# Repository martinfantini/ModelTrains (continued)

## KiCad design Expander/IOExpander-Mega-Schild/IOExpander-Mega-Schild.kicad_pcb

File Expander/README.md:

# Expander

This repository contains all the necesarry information for generate an expander of the possible input/output of the central.

## IO-Expander

For this case, I use also the [EX-IOExpander](https://github.com/DCC-EX/EX-IOExpander)

## Generic-Mega-Schild

For my case, I yunse Arduino Mega shild to generate the expander. To have more clean, the expande, I generate a circuit borad to solder all the input cables.

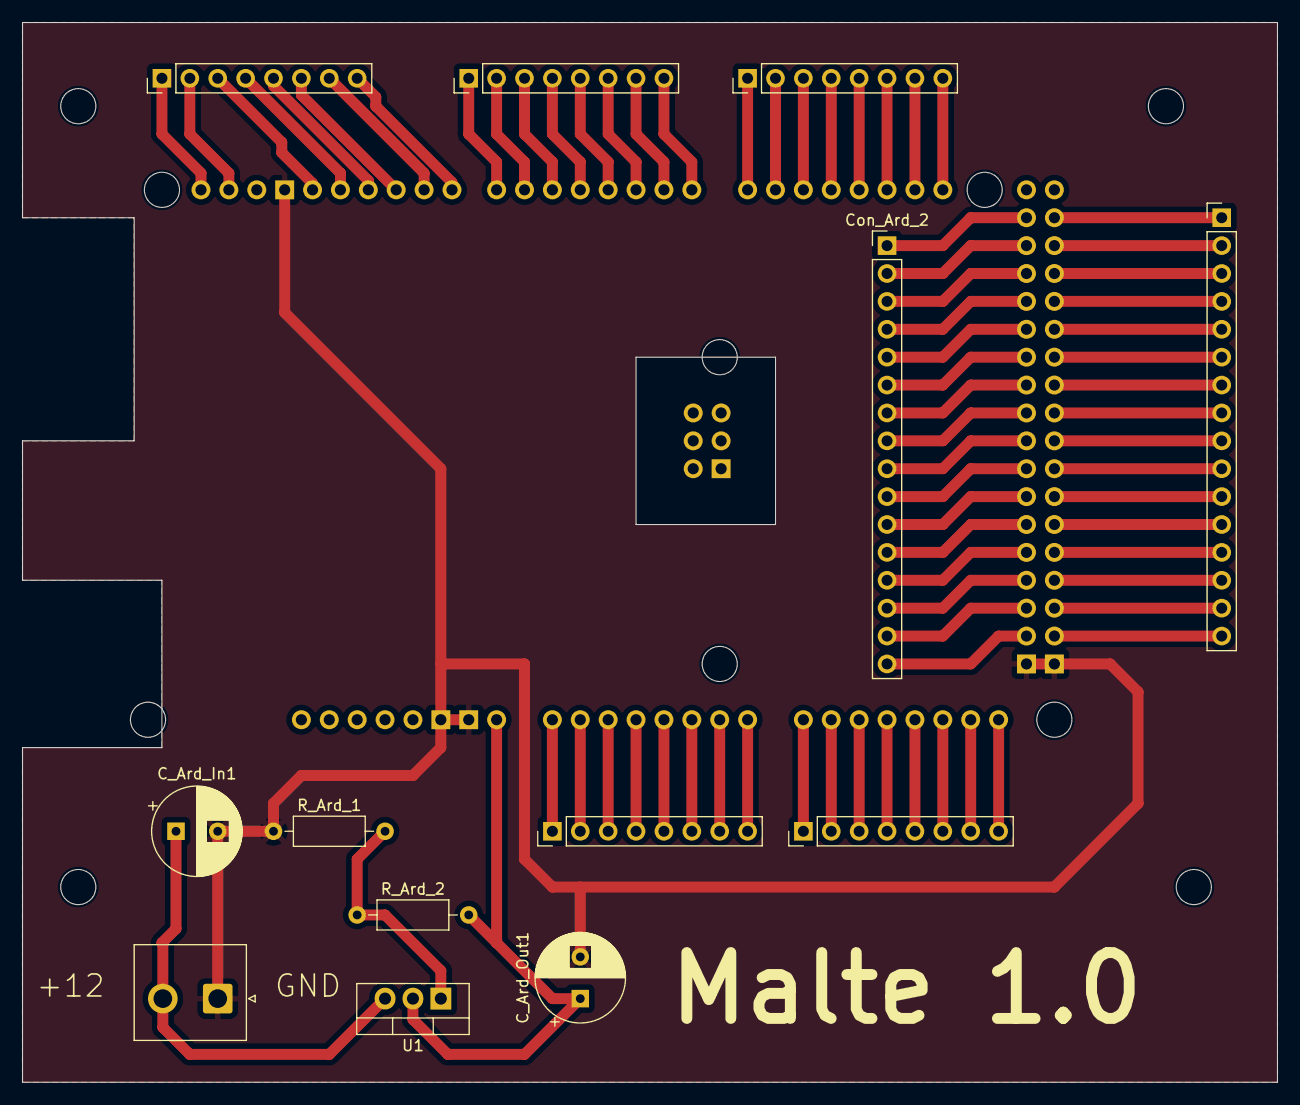
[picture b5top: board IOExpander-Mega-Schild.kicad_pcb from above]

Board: 2 copper layers, 114.3 x 96.5 mm, 14 parts (0 on the bottom side), 76 nets.

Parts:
CON_In1: DCC; JST_NV_B02P-NV_1x02_P5.00mm_Vertical
C_Ard_In1: 10uF; CP_Radial_D8.0mm_P3.80mm
C_Ard_Out1: 10uF; CP_Radial_D8.0mm_P3.80mm
Central1: Arduino_Mega2560_Shield
Con_Ard_2, Con_Ard_3: Conn_01x16; PinHeader_1x16_P2.54mm_Vertical
J1, J2, J3, J4, J5: Conn_01x08; PinHeader_1x08_P2.54mm_Vertical
R_Ard_1: 3K9; R_Axial_DIN0207_L6.3mm_D2.5mm_P10.16mm_Horizontal
R_Ard_2: 560; R_Axial_DIN0207_L6.3mm_D2.5mm_P10.16mm_Horizontal
U1: LD1086V-DG; TO-220-3_Vertical

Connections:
+12V: CON_In1.2, C_Ard_In1.1, U1.3 (IN)
Earth: CON_In1.1, C_Ard_In1.2, C_Ard_Out1.2, Central1.GND1 (GND), Central1.GND2 (GND), Central1.GND3 (GND), Central1.GND5 (GND), Central1.GND6 (GND), R_Ard_1.1
unnamed: Central1.D0 (D0_RX0), J4.8
unnamed: Central1.D1 (D1_TX0), J4.7
unnamed: Central1.D2 (D2_INT0), J4.6
unnamed: Central1.D3 (D3_INT1), J4.5
unnamed: Central1.D14 (D14_TX3), J3.1
unnamed: Central1.D15 (D15_RX3), J3.2
unnamed: Central1.D16 (D16_TX2), J3.3
unnamed: Central1.D17 (D17_RX2), J3.4
unnamed: Central1.D18 (D18_TX1), J3.5
unnamed: Central1.D19 (D19_RX1), J3.6
unnamed: Central1.D20 (D20_SDA), J3.7
unnamed: Central1.D21 (D21_SCL), J3.8
unnamed: Central1.D53 (D53_SS), Con_Ard_3.16
unnamed: Central1.D22, Con_Ard_2.1
unnamed: Central1.D24, Con_Ard_2.2
unnamed: Central1.D26, Con_Ard_2.3
unnamed: Central1.D28, Con_Ard_2.4
unnamed: Central1.D30, Con_Ard_2.5
unnamed: Central1.D32, Con_Ard_2.6
unnamed: Central1.D34, Con_Ard_2.7
unnamed: Central1.D36, Con_Ard_2.8
unnamed: Central1.D38, Con_Ard_2.9
unnamed: Central1.D40, Con_Ard_2.10
unnamed: Central1.D42, Con_Ard_2.11
unnamed: Central1.D44, Con_Ard_2.12
unnamed: Central1.D46, Con_Ard_2.13
unnamed: Central1.D48, Con_Ard_2.14
unnamed: Central1.D50, Con_Ard_2.15
unnamed: Central1.D52, Con_Ard_2.16
unnamed: Central1.D23, Con_Ard_3.1
unnamed: Central1.D25, Con_Ard_3.2
unnamed: Central1.D27, Con_Ard_3.3
unnamed: Central1.D29, Con_Ard_3.4
unnamed: Central1.D31, Con_Ard_3.5
unnamed: Central1.D33, Con_Ard_3.6
unnamed: Central1.D35, Con_Ard_3.7
unnamed: Central1.D37, Con_Ard_3.8
unnamed: Central1.D39, Con_Ard_3.9
unnamed: Central1.D41, Con_Ard_3.10
unnamed: Central1.D43, Con_Ard_3.11
unnamed: Central1.D45, Con_Ard_3.12
unnamed: Central1.D47, Con_Ard_3.13
unnamed: Central1.D49, Con_Ard_3.14
unnamed: Central1.D51, Con_Ard_3.15
unnamed: Central1.A0, J1.1
unnamed: Central1.A1, J1.2
unnamed: Central1.A2, J1.3
unnamed: Central1.A3, J1.4
unnamed: Central1.A4, J1.5
unnamed: Central1.A5, J1.6
unnamed: Central1.A6, J1.7
unnamed: Central1.A7, J1.8
unnamed: Central1.A8, J2.1
unnamed: Central1.A9, J2.2
unnamed: Central1.A10, J2.3
unnamed: Central1.A11, J2.4
unnamed: Central1.A12, J2.5
unnamed: Central1.A13, J2.6
unnamed: Central1.A14, J2.7
unnamed: Central1.A15, J2.8
unnamed: Central1.D7, J4.1
unnamed: Central1.D6, J4.2
unnamed: Central1.D5, J4.3
unnamed: Central1.D4, J4.4
unnamed: Central1.SCL, J5.1
unnamed: Central1.SDA, J5.2
unnamed: Central1.D13, J5.3
unnamed: Central1.D12, J5.4
unnamed: Central1.D11, J5.5
unnamed: Central1.D10, J5.6
unnamed: Central1.D9, J5.7
unnamed: Central1.D8, J5.8
unnamed: R_Ard_1.2, R_Ard_2.1, U1.1 (ADJ/GND)
unnamed: C_Ard_Out1.1, Central1.VIN, R_Ard_2.2, U1.2 (OUT)

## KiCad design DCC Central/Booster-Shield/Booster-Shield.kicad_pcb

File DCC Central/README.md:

# DCC Central

As a DCC central, I use the open source project [CommandStation-EX](https://github.com/DCC-EX/CommandStation-EX), here is added as asubmodule up this project.
Usigin Arduino ATMega 328, I generate a booster with the use of the motor diver [BTS7960](./'BTS7960 Motor Driver.pdf')

## CommandStation-EX

Here is the CommandStation-EX project used to generate the DCC central, which will be user to control all the trains and diferent periferics asociated to the DCC protocol.

## Booster

In this folder contains the source code to coltrol the booster with the ATMega 328.

## Booster-Shield

In this folder contains the circuit board to control the [motor driver](./'BTS7960 Motor Driver.pdf')

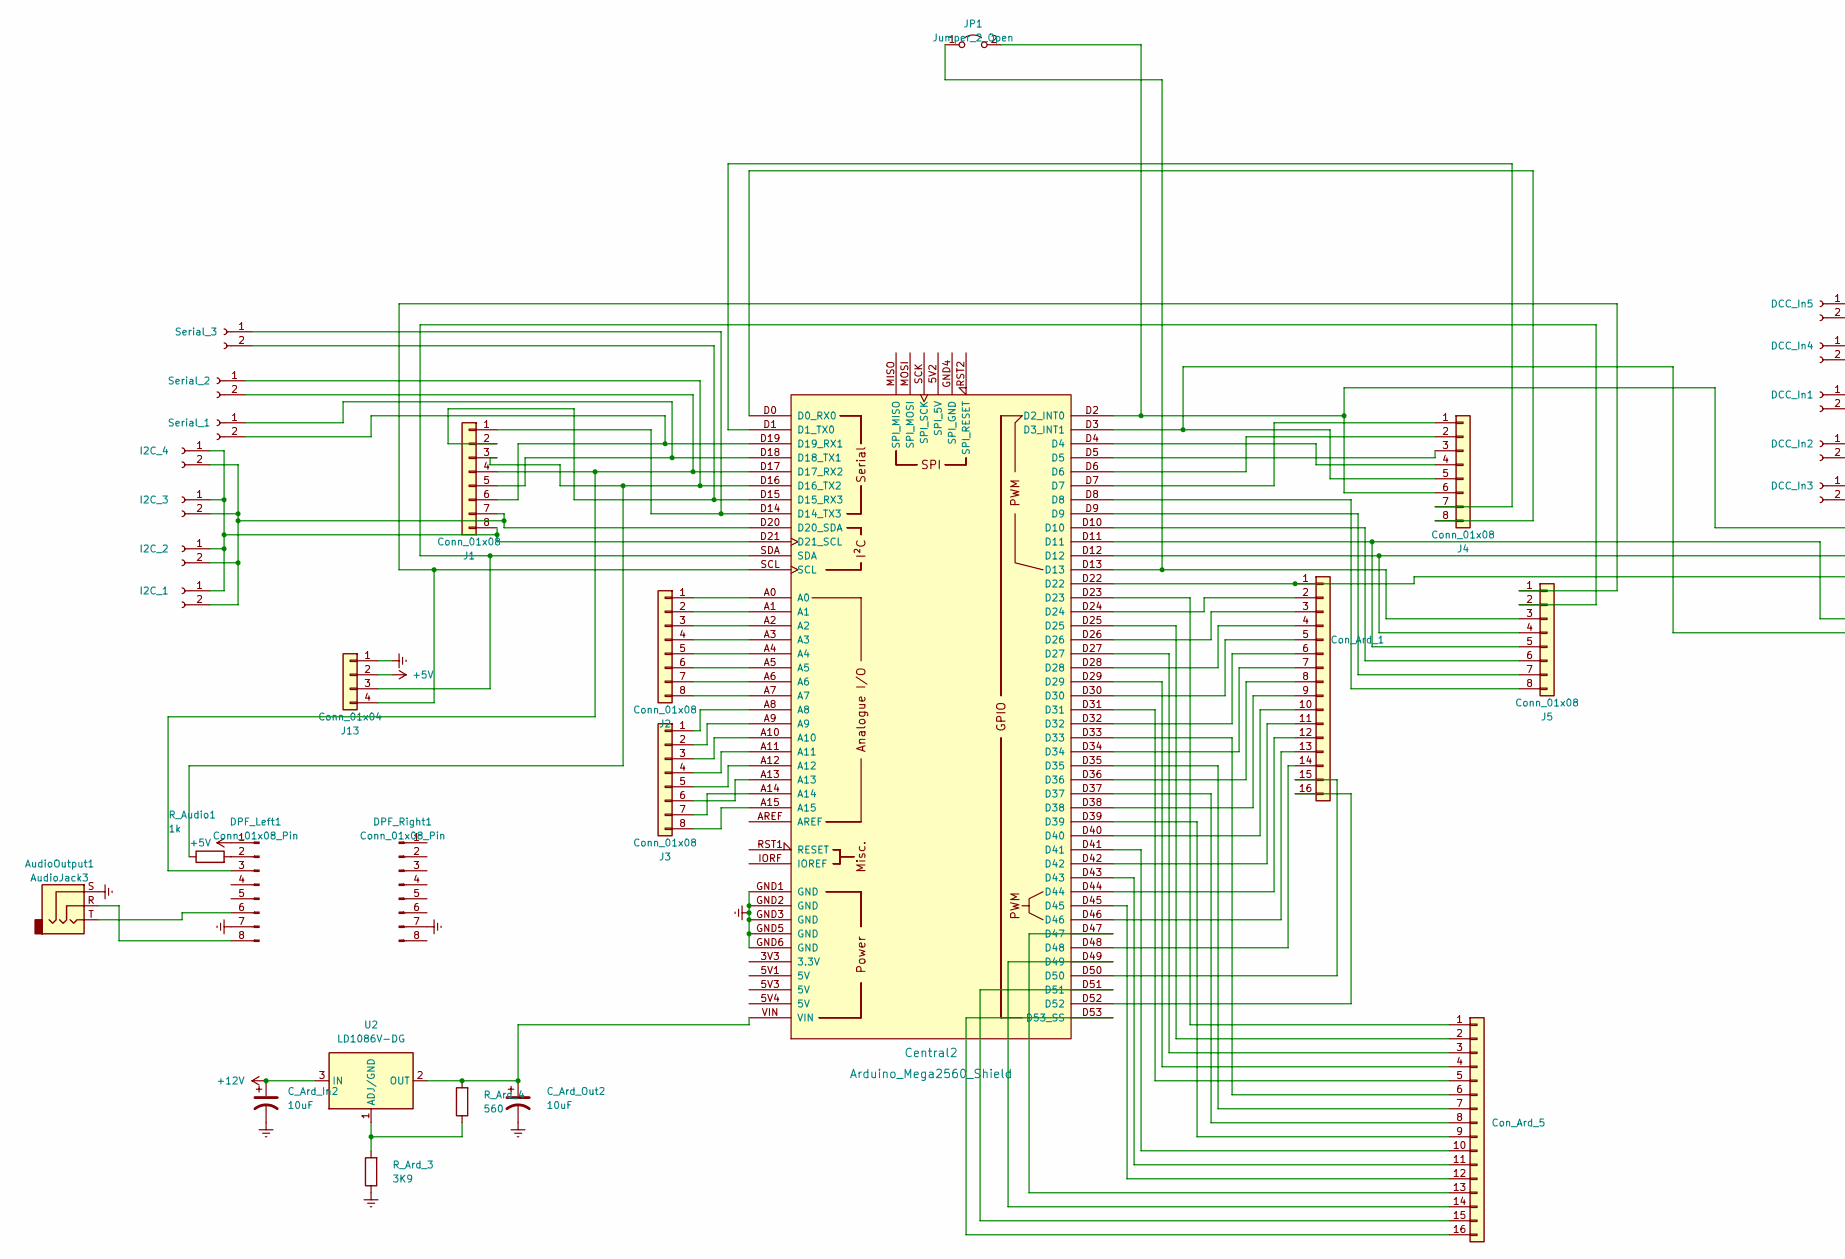
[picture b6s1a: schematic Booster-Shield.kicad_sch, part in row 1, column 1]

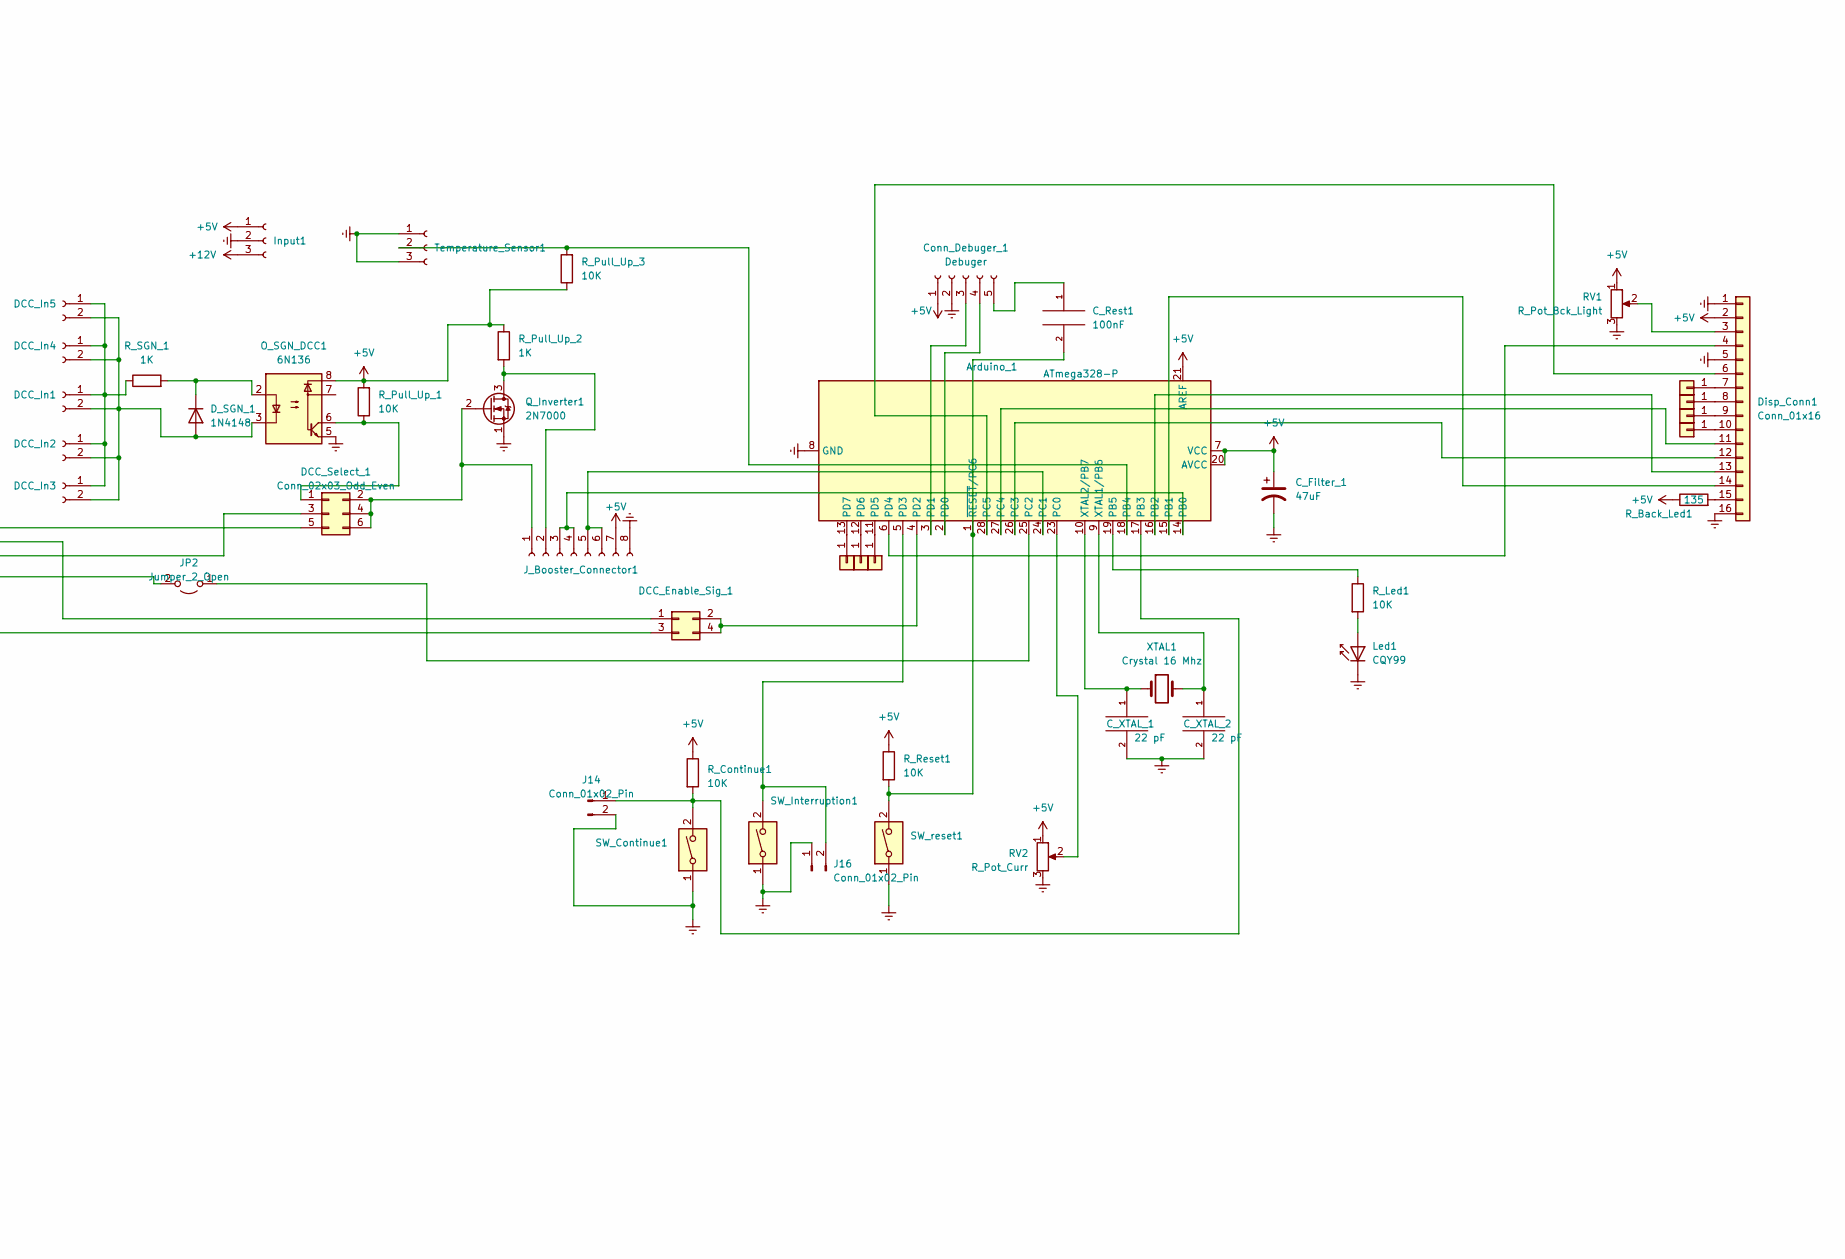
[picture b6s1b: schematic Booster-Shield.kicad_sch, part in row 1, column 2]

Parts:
Arduino_1: ATmega328-P; DIP-28_W7.62mm
AudioOutput1: AudioJack3; Jack_3.5mm_CUI_SJ1-3523N_Horizontal
C_Ard_In2: 10uF; CP_Radial_D8.0mm_P3.80mm
C_Ard_Out2: 10uF; CP_Radial_D8.0mm_P3.80mm
C_Filter_1: 47uF; CP_Radial_D8.0mm_P3.80mm
C_Rest1: 100nF; C_2225_5664Metric_Pad1.80x6.60mm_HandSolder
C_XTAL_1, C_XTAL_2: 22 pF; C_Disc_D8.0mm_W5.0mm_P5.00mm
Central2: Arduino_Mega2560_Shield
Con_Ard_1, Con_Ard_5: Conn_01x16; PinHeader_1x16_P2.54mm_Vertical
Conn_Debuger_1: Debuger; PinHeader_1x05_P2.54mm_Vertical
DCC_Enable_Sig_1: Conn_02x02_Odd_Even; PinHeader_2x02_P2.54mm_Vertical
DCC_In1, DCC_In2, DCC_In3, DCC_In4, DCC_In5: DCC; Wago_734-132_1x02_P3.50mm_Vertical
DCC_Select_1: Conn_02x03_Odd_Even; PinHeader_2x03_P2.54mm_Vertical
DPF_Left1: Conn_01x08_Pin; PinHeader_1x08_P2.54mm_Vertical
DPF_Right1: Conn_01x08_Pin; PinHeader_1x08_P2.54mm_Vertical
D_SGN_1: 1N4148; D_DO-35_SOD27_P7.62mm_Horizontal
Disp_Conn1: Conn_01x16; PinHeader_1x16_P2.54mm_Vertical
I2C_1, I2C_2, I2C_3, I2C_4: I2C; Wago_734-132_1x02_P3.50mm_Vertical
Input1: Conn_01x03_Female; JST_NV_B03P-NV_1x03_P5.00mm_Vertical
J1, J2, J3, J4, J5: Conn_01x08; PinHeader_1x08_P2.54mm_Vertical
J6, J7, J8, J9, J10, J11, J12: Conn_01x01; PinHeader_1x01_P2.54mm_Vertical
J13: Conn_01x04; PinHeader_1x04_P2.54mm_Vertical
J14, J16: Conn_01x02_Pin; PinHeader_1x02_P2.54mm_Vertical
JP1, JP2: Jumper_2_Open; SolderJumper-2_P1.3mm_Open_Pad1.0x1.5mm
J_Booster_Connector1: Conn_01x08_Female; PinHeader_2x04_P2.54mm_Vertical
Led1: CQY99; LED_D5.0mm_IRGrey
O_SGN_DCC1: 6N136; DIP-8_W7.62mm
Q_Inverter1: 2N7000; TO-92_Inline
RV1: R_Pot_Bck_Light; Potentiometer_ACP_CA6-H2,5_Horizontal
RV2: R_Pot_Curr; Potentiometer_ACP_CA6-H2,5_Horizontal
R_Ard_3: 3K9; R_Axial_DIN0207_L6.3mm_D2.5mm_P10.16mm_Horizontal
R_Ard_4: 560; R_Axial_DIN0207_L6.3mm_D2.5mm_P10.16mm_Horizontal
R_Audio1: 1k; R_Axial_DIN0207_L6.3mm_D2.5mm_P10.16mm_Horizontal
R_Back_Led1: 135; R_Axial_DIN0207_L6.3mm_D2.5mm_P10.16mm_Horizontal
R_Continue1: 10K; R_Axial_DIN0207_L6.3mm_D2.5mm_P10.16mm_Horizontal
R_Led1: 10K; R_Axial_DIN0207_L6.3mm_D2.5mm_P10.16mm_Horizontal
R_Pull_Up_1, R_Pull_Up_3: 10K; R_Axial_DIN0207_L6.3mm_D2.5mm_P10.16mm_Horizontal
R_Pull_Up_2: 1K; R_Axial_DIN0207_L6.3mm_D2.5mm_P10.16mm_Horizontal
R_Reset1: 10K; R_Axial_DIN0207_L6.3mm_D2.5mm_P10.16mm_Horizontal
R_SGN_1: 1K; R_Axial_DIN0207_L6.3mm_D2.5mm_P10.16mm_Horizontal
SW_Continue1: SW_DIP_x01; SW_PUSH_6mm_H5mm
SW_Interruption1: SW_DIP_x01; SW_PUSH_6mm_H5mm
SW_reset1: SW_DIP_x01; SW_PUSH_6mm_H5mm
Serial_1, Serial_2, Serial_3: Serial; Wago_734-132_1x02_P3.50mm_Vertical
Temperature_Sensor1: Conn_01x03_Female; JST_EH_B3B-EH-A_1x03_P2.50mm_Vertical
U2: LD1086V-DG; TO-220-3_Vertical
XTAL1: Crystal 16 Mhz; Crystal_HC49-U_Vertical

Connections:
+5V: Arduino_1.7 (VCC), Arduino_1.20 (AVCC), Arduino_1.21 (AREF), C_Filter_1.1, Conn_Debuger_1.1, DPF_Left1.1, Disp_Conn1.2, Input1.1, J13.2, J_Booster_Connector1.7, O_SGN_DCC1.8, RV1.1, RV2.1, R_Back_Led1.1, R_Continue1.1, R_Pull_Up_1.2, R_Pull_Up_2.1, R_Pull_Up_3.1, R_Reset1.1
+12V: C_Ard_In2.1, Input1.3, U2.3 (IN)
Earth: Arduino_1.8 (GND), Arduino_1.22 (GND), AudioOutput1.S, C_Ard_In2.2, C_Ard_Out2.2, C_Filter_1.2, C_XTAL_1.2, C_XTAL_2.2, Central2.GND1 (GND), Central2.GND2 (GND), Central2.GND3 (GND), Central2.GND5 (GND), Central2.GND6 (GND), Conn_Debuger_1.2, DPF_Left1.7, DPF_Right1.7, Disp_Conn1.1, Disp_Conn1.5, Disp_Conn1.16, Input1.2, J13.1, J14.2, J16.1, J_Booster_Connector1.8, Led1.1 (K), O_SGN_DCC1.5, Q_Inverter1.1 (S), RV1.3, RV2.3, R_Ard_3.1, SW_Continue1.1, SW_Interruption1.1, SW_reset1.1, Temperature_Sensor1.1, Temperature_Sensor1.3
unnamed: Arduino_1.14 (PB0), J_Booster_Connector1.3, J_Booster_Connector1.4
unnamed: Arduino_1.15 (PB1), Disp_Conn1.14
unnamed: Arduino_1.16 (PB2), Disp_Conn1.13
unnamed: Arduino_1.17 (PB3), J14.1, R_Continue1.2, SW_Continue1.2
unnamed: Arduino_1.18 (PB4), R_Pull_Up_3.2, Temperature_Sensor1.2
unnamed: Arduino_1.19 (PB5), R_Led1.1
unnamed: Arduino_1.23 (PC0), RV2.2
unnamed: Arduino_1.24 (PC1), J_Booster_Connector1.5, J_Booster_Connector1.6
unnamed: Arduino_1.25 (PC2), JP2.1 (A)
unnamed: Arduino_1.26 (PC3), Disp_Conn1.12
unnamed: Arduino_1.27 (PC4), Disp_Conn1.11
unnamed: Arduino_1.28 (PC5), Disp_Conn1.6
unnamed: Arduino_1.2 (PD0), Conn_Debuger_1.4
unnamed: Arduino_1.3 (PD1), Conn_Debuger_1.3
unnamed: Arduino_1.4 (PD2), DCC_Enable_Sig_1.2, DCC_Enable_Sig_1.4
unnamed: Arduino_1.5 (PD3), J16.2, SW_Interruption1.2
unnamed: Arduino_1.6 (PD4), Disp_Conn1.4
unnamed: Arduino_1.11 (PD5), J6.1
unnamed: Arduino_1.12 (PD6), J7.1
unnamed: Arduino_1.13 (PD7), J8.1
unnamed: Arduino_1.9 (XTAL1/PB6), C_XTAL_2.1, XTAL1.2
unnamed: Arduino_1.10 (XTAL2/PB7), C_XTAL_1.1, XTAL1.1
unnamed: Arduino_1.1 (~RESET/PC6), C_Rest1.2, R_Reset1.2, SW_reset1.2
unnamed: Central2.D0 (D0_RX0), J4.8
unnamed: Central2.D1 (D1_TX0), J4.7
unnamed: Central2.D2 (D2_INT0), DCC_Select_1.5, J4.6, JP1.2 (B)
unnamed: Central2.D3 (D3_INT1), DCC_Enable_Sig_1.3, J4.5
unnamed: Central2.D14 (D14_TX3), J1.1, Serial_3.1
unnamed: Central2.D15 (D15_RX3), J1.2, Serial_3.2
unnamed: Central2.D16 (D16_TX2), J1.3, R_Audio1.1, Serial_2.1
unnamed: Central2.D17 (D17_RX2), DPF_Left1.3, J1.4, Serial_2.2
unnamed: Central2.D18 (D18_TX1), J1.5, Serial_1.1
unnamed: Central2.D19 (D19_RX1), J1.6, Serial_1.2
unnamed: Central2.D20 (D20_SDA), I2C_1.2, I2C_2.2, I2C_3.2, I2C_4.2, J1.7
unnamed: Central2.D21 (D21_SCL), I2C_1.1, I2C_2.1, I2C_3.1, I2C_4.1, J1.8
unnamed: Central2.D53 (D53_SS), Con_Ard_5.16
unnamed: Central2.D22, Con_Ard_1.1, JP2.2 (B)
unnamed: Central2.D24, Con_Ard_1.2
unnamed: Central2.D26, Con_Ard_1.3
unnamed: Central2.D28, Con_Ard_1.4
unnamed: Central2.D30, Con_Ard_1.5
unnamed: Central2.D32, Con_Ard_1.6
unnamed: Central2.D34, Con_Ard_1.7
unnamed: Central2.D36, Con_Ard_1.8
unnamed: Central2.D38, Con_Ard_1.9
unnamed: Central2.D40, Con_Ard_1.10
unnamed: Central2.D42, Con_Ard_1.11
unnamed: Central2.D44, Con_Ard_1.12
unnamed: Central2.D46, Con_Ard_1.13
unnamed: Central2.D48, Con_Ard_1.14
unnamed: Central2.D50, Con_Ard_1.15
unnamed: Central2.D52, Con_Ard_1.16
unnamed: Central2.D23, Con_Ard_5.1
unnamed: Central2.D25, Con_Ard_5.2
unnamed: Central2.D27, Con_Ard_5.3
unnamed: Central2.D29, Con_Ard_5.4
unnamed: Central2.D31, Con_Ard_5.5
unnamed: Central2.D33, Con_Ard_5.6
unnamed: Central2.D35, Con_Ard_5.7
unnamed: Central2.D37, Con_Ard_5.8
unnamed: Central2.D39, Con_Ard_5.9
unnamed: Central2.D41, Con_Ard_5.10
unnamed: Central2.D43, Con_Ard_5.11
unnamed: Central2.D45, Con_Ard_5.12
unnamed: Central2.D47, Con_Ard_5.13
unnamed: Central2.D49, Con_Ard_5.14
unnamed: Central2.D51, Con_Ard_5.15
unnamed: C_Rest1.1, Conn_Debuger_1.5
unnamed: Central2.D11, DCC_Enable_Sig_1.1, J5.5
unnamed: DCC_In1.1, DCC_In2.1, DCC_In3.1, DCC_In4.1, DCC_In5.1, R_SGN_1.1
unnamed: DCC_In1.2, DCC_In2.2, DCC_In3.2, DCC_In4.2, DCC_In5.2, D_SGN_1.2 (A), O_SGN_DCC1.3
unnamed: DCC_Select_1.1, O_SGN_DCC1.6, R_Pull_Up_1.1
unnamed: DCC_Select_1.2, DCC_Select_1.4, DCC_Select_1.6, J_Booster_Connector1.1, Q_Inverter1.2 (G)
unnamed: Central2.D12, DCC_Select_1.3, J5.4
unnamed: DPF_Left1.2, R_Audio1.2
unnamed: AudioOutput1.T, DPF_Left1.6
unnamed: AudioOutput1.R, DPF_Left1.8
unnamed: D_SGN_1.1 (K), O_SGN_DCC1.2, R_SGN_1.2
unnamed: Disp_Conn1.3, RV1.2
unnamed: Disp_Conn1.7, J9.1
unnamed: Disp_Conn1.8, J10.1
unnamed: Disp_Conn1.9, J11.1
unnamed: Disp_Conn1.10, J12.1
unnamed: Disp_Conn1.15, R_Back_Led1.2
unnamed: Central2.A0, J2.1
unnamed: Central2.A1, J2.2
unnamed: Central2.A2, J2.3
unnamed: Central2.A3, J2.4
unnamed: Central2.A4, J2.5
unnamed: Central2.A5, J2.6
unnamed: Central2.A6, J2.7
unnamed: Central2.A7, J2.8
unnamed: Central2.A8, J3.1
unnamed: Central2.A9, J3.2
unnamed: Central2.A10, J3.3
unnamed: Central2.A11, J3.4
unnamed: Central2.A12, J3.5
unnamed: Central2.A13, J3.6
unnamed: Central2.A14, J3.7
unnamed: Central2.A15, J3.8
unnamed: Central2.D7, J4.1
unnamed: Central2.D6, J4.2
unnamed: Central2.D5, J4.3
unnamed: Central2.D4, J4.4
unnamed: Central2.D13, J5.3, JP1.1 (A)
unnamed: Central2.D10, J5.6
unnamed: Central2.D9, J5.7
unnamed: Central2.D8, J5.8
unnamed: Central2.SDA, J5.2, J13.3
unnamed: Central2.SCL, J5.1, J13.4
unnamed: J_Booster_Connector1.2, Q_Inverter1.3 (D), R_Pull_Up_2.2
unnamed: Led1.2 (A), R_Led1.2
unnamed: R_Ard_3.2, R_Ard_4.1, U2.1 (ADJ/GND)
unnamed: C_Ard_Out2.1, Central2.VIN, R_Ard_4.2, U2.2 (OUT)

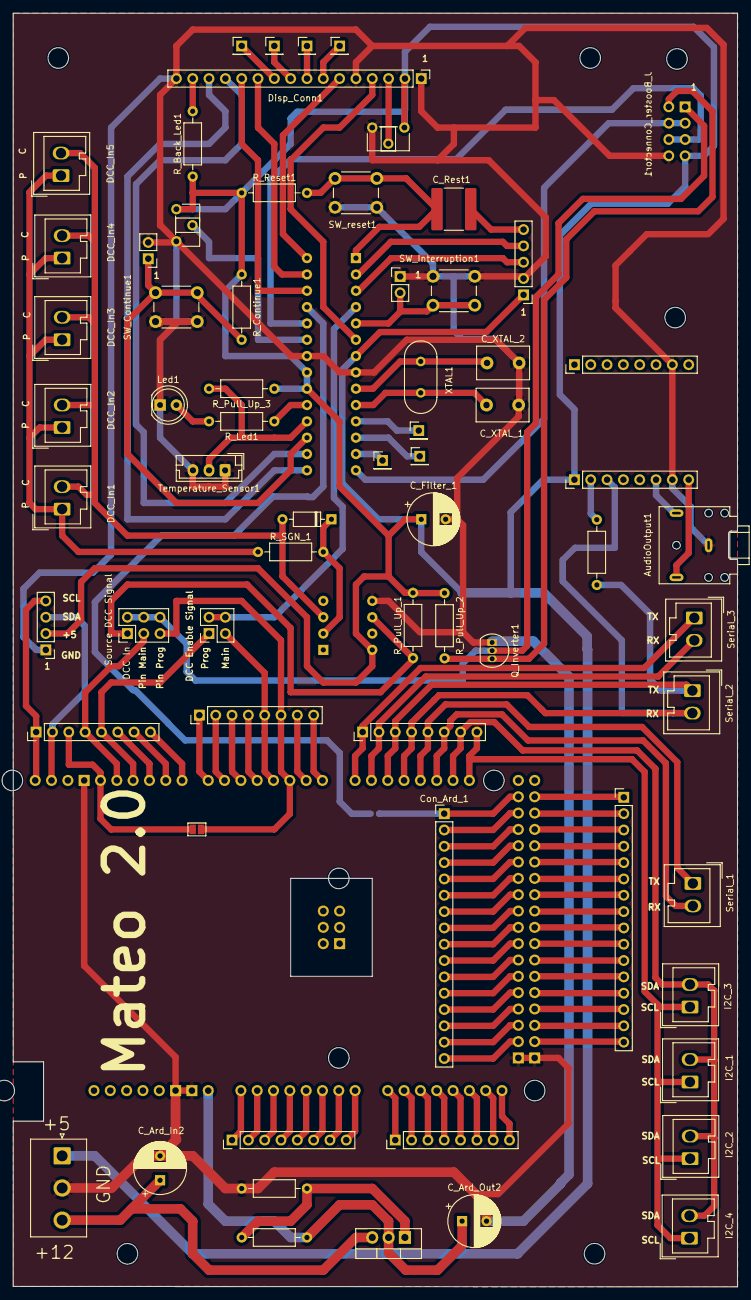
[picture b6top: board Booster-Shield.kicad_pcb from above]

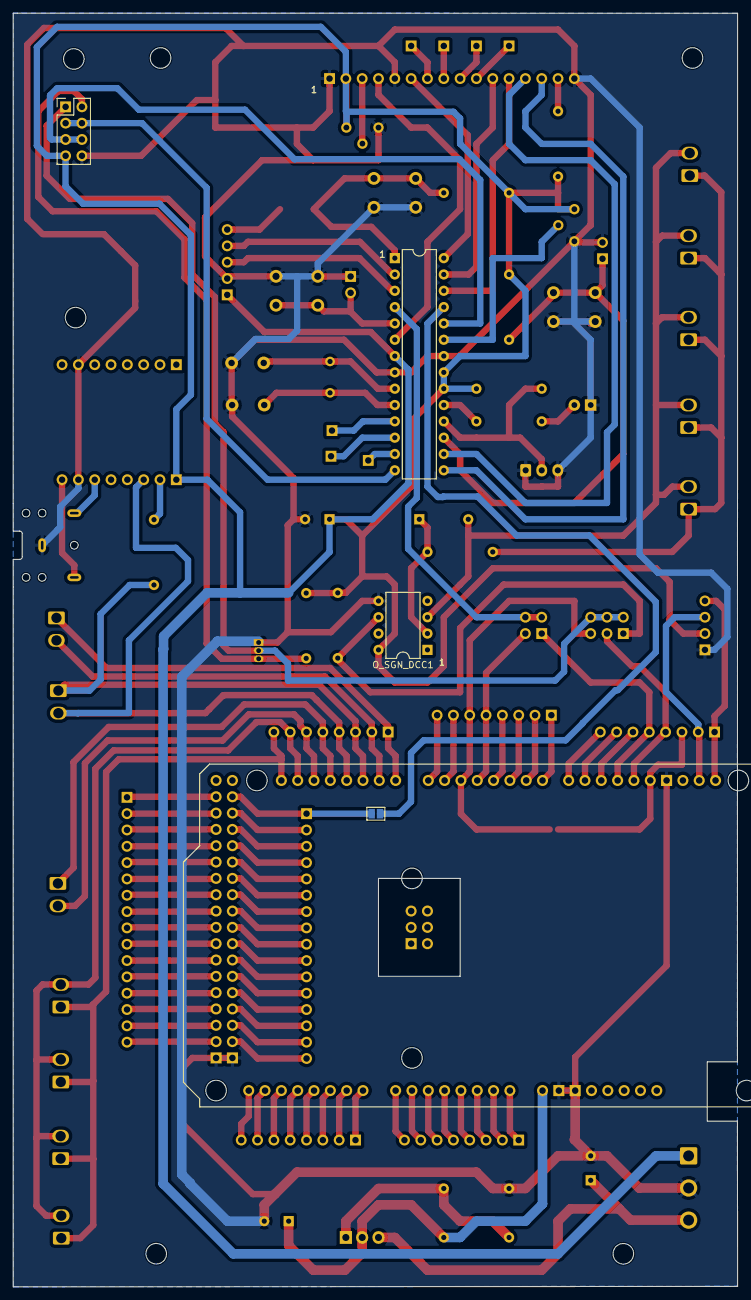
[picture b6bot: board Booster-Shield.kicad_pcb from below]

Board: 2 copper layers, 112.7 x 198.2 mm, 71 parts (4 on the bottom side), 117 nets.

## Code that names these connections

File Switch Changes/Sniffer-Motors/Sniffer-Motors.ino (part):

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#define DEBUG_DCC

//DCC Signal
#define DCC_ACK_SIGNAL 3  // Pin 5 - PD3
#define DCC_PIN_IN     2  // Pin 4 - PD2

//Motor 1
#define PIN_MOTOR_1_PIN_1 7 // Pin 13 - PD7
#define PIN_MOTOR_1_PIN_2 6 // Pin 12 - PD6

//Motor 2
#define PIN_MOTOR_2_PIN_1 4 // Pin 11 - PD5
#define PIN_MOTOR_2_PIN_2 5 // Pin 6  - PD4

//Motor 3
#define PIN_MOTOR_3_PIN_1 A5 // Pin 28 - PC5 
#define PIN_MOTOR_3_PIN_2 A2 // Pin 25 - PC1

//Motor 4
#define PIN_MOTOR_4_PIN_1 A3 // Pin 26 - PC3
#define PIN_MOTOR_4_PIN_2 A4 // Pin 27 - PC4

//Motor 5
#define PIN_MOTOR_5_PIN_1 13 // Pin 19 - PB5 
#define PIN_MOTOR_5_PIN_2 12 // Pin 18 - PB4

//Motor 6
#define PIN_MOTOR_6_PIN_1 A1 // Pin 23 - PC0
#define PIN_MOTOR_6_PIN_2 A0 // Pin 24 - PD7

//Motor 7
#define PIN_MOTOR_7_PIN_1 9 // Pin 15 - PB1 
#define PIN_MOTOR_7_PIN_2 8 // Pin 14 - PB0

//Motor 8
#define PIN_MOTOR_8_PIN_1 10 // Pin 17 - PB3
#define PIN_MOTOR_8_PIN_2 11 // Pin 16 - PB2

NmraDcc Dcc;

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
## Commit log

2024-01-19 Add the basis and the DCC central repository
2024-01-19 Add DCC Central to the repository
2024-01-19 Add the expander information
2024-01-19 Add the circuit board and the code for the lignts
2024-01-19 Correct the link to the datascheet
2024-01-19 Add theblock detector board
2024-01-19 Update the comment
2024-01-19 Add DCC signal circuit board
2024-01-19 Add switch changes motor board control
2024-02-18 Sprelling correct and order the CV / Values position in the definition
2024-03-09 Refactor the code to support bliking effect
2024-03-16 Add intial state of the signal and correct the bliking effect
2024-04-25 Add the configuration of the on lights for differents configurations
2024-05-07 Add the new version of the program with Arnet library
2024-05-08 Our configuration
2024-05-20 Correct the low part of the comparation
2024-05-20 Improve the code using shift operators
2024-05-20 Update the Readme and the comments of the code
2024-05-24 Add arnet with the arduino arnet library
2026-01-04 Generate a funtion for the efect
2026-01-04 Update the signal script: make the reuse the code and correct turn off of the lights
